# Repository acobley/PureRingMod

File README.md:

View this project on [CADLAB.io](https://cadlab.io/project/1337). 

# PureRingMod
A Eurorack ring modulator.

1:  Balanced input suitable for a SM58 
2: Carrier and Mod levels should accept 10Vpp.   Level controls on each.
3: Mixer on Mic in and Carrier
4: Mixer on the output of the ring mod chip and Carrier in.  This allows the uint to act as a mic input to eurorack
5: Gain control on the output stage, I found this useful to avoid clipping on the output
6: Dual output sockets.  It's a bugbear of mine that more modules don't have dual output to avoid having to use a splitter module to send the signal to more than one output.

Design Andy C
From a design by Roman Sowa
CC BY 3.0

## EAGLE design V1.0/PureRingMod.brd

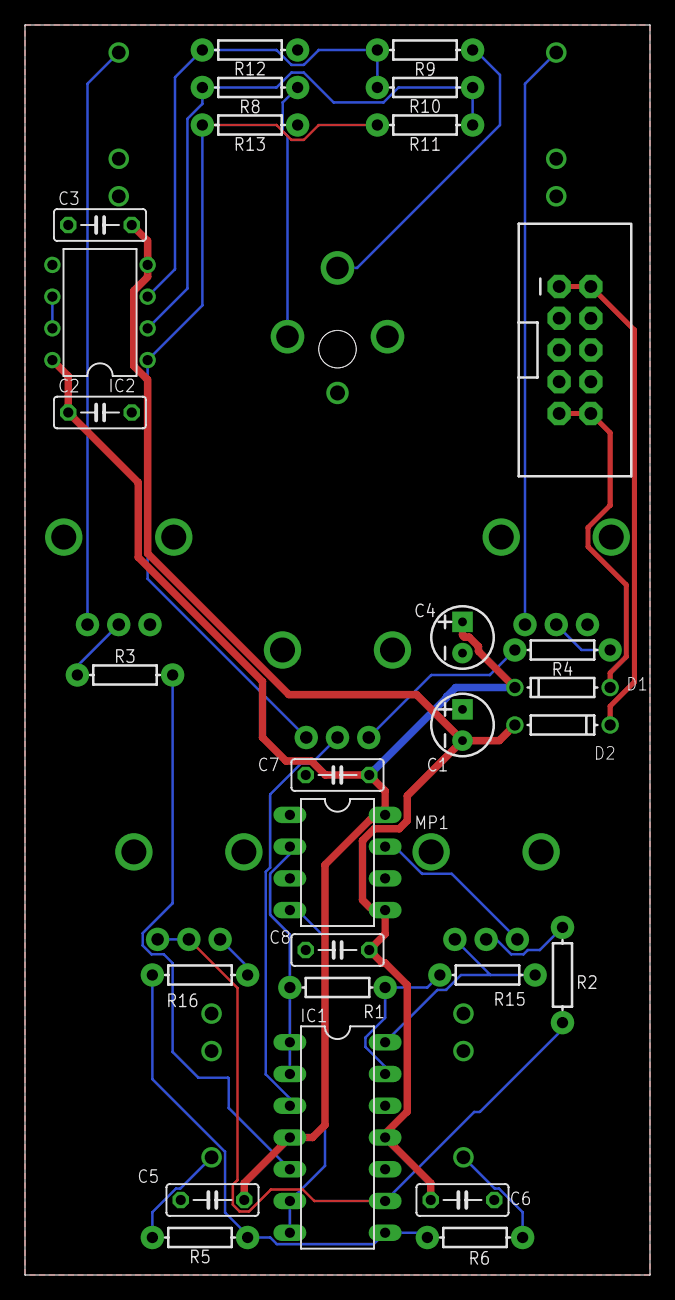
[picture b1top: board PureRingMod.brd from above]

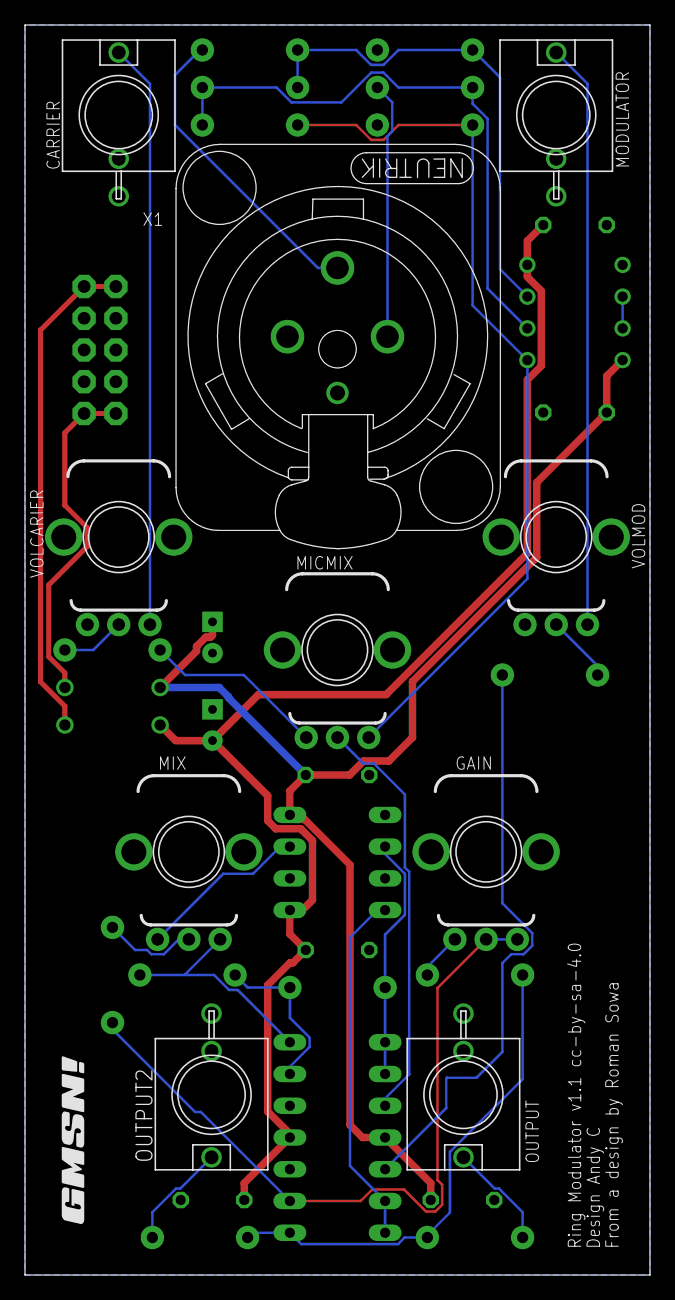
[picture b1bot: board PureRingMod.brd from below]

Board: 2 copper layers, 50.0 x 100.0 mm, 39 parts (11 on the bottom side), 29 nets.

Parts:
C1, C4: 10uF; CPOL-RADIAL-2.5MM-5MM
C2, C3, C5, C6, C7, C8: C050-025X075
CARRIER: JACK
D1: 1n4148; DO-1N4148
D2: 1N4148; DO-1N4148
GAIN: 9MMPOT; POT
IC1: TL074P; DIL14
IC2: TL072P; DIL08
MICMIX: 9MMPOT; POT
MIX: 9MMPOT; POT
MODULATOR: JACK
MP1: AD633-2_AD633AN; AD633-2_DIL08
OUTPUT: JACK
OUTPUT2: Output2; JACK
POWER: M05X2SHD; 2X5-SHROUDED
R1, R2, R3, R4, R5, R6, R8, R9, R10, R11, R12, R13, R15, R16: 330; AXIAL-0.3
U$2: GMSN!_LOGO
VOLCARIER: 9MMPOT; POT
VOLMOD: 9MMPOT; POT
X1: CON-NEUTRIK_AG_NC3FD-V

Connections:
+12V: C2.1, C4.1, C5.1, C7.1, D1.C, IC1.4, IC2.8, MP1.8
-12V: C1.2, C3.2, C6.2, C8.2, D2.A, IC1.11, IC2.4, MP1.5
GND: C1.1, C2.2, C3.1, C4.2, C5.2, C6.1, C7.2, C8.1, CARRIER.GND, CARRIER.NORM, IC1.10, IC1.12, IC2.5, MODULATOR.GND, MODULATOR.NORM, MP1.1, MP1.3, MP1.6, OUTPUT.GND, OUTPUT2.GND, POWER.3, POWER.4, POWER.5, POWER.6, POWER.7, POWER.8, R12.P$2, R13.P$1, VOLCARIER.P$1, VOLMOD.P$1, X1.1, X1.G
unnamed: IC1.1, IC1.2, MP1.2, R1.P$1
unnamed: IC1.6, IC1.7, MP1.4
unnamed: MIX.P$1, MP1.7
unnamed: IC1.14, MIX.P$3, R15.P$2
unnamed: GAIN.P$1, R16.P$1
unnamed: MIX.P$2, R2.P$1
unnamed: GAIN.P$2, GAIN.P$3, IC1.9, R2.P$2
unnamed: MICMIX.P$1, R4.P$2
unnamed: D1.A, POWER.9, POWER.10
unnamed: D2.C, POWER.1, POWER.2
unnamed: IC1.5, R3.P$2
unnamed: IC1.8, R5.P$1, R6.P$1, R16.P$2
unnamed: IC2.6, IC2.7
unnamed: IC1.13, R1.P$2, R15.P$1
unnamed: OUTPUT.TIP, R5.P$2
unnamed: CARRIER.TIP, VOLCARIER.P$3
unnamed: MODULATOR.TIP, VOLMOD.P$3
unnamed: R4.P$1, VOLCARIER.P$2
unnamed: R3.P$1, VOLMOD.P$2
unnamed: OUTPUT2.TIP, R6.P$2
unnamed: R8.P$1, X1.2
unnamed: R9.P$1, X1.3
unnamed: IC2.2, R8.P$2, R10.P$2, R11.P$1
unnamed: IC2.3, R9.P$2, R10.P$1, R12.P$1
unnamed: IC2.1, MICMIX.P$3, R11.P$2, R13.P$2
unnamed: IC1.3, MICMIX.P$2

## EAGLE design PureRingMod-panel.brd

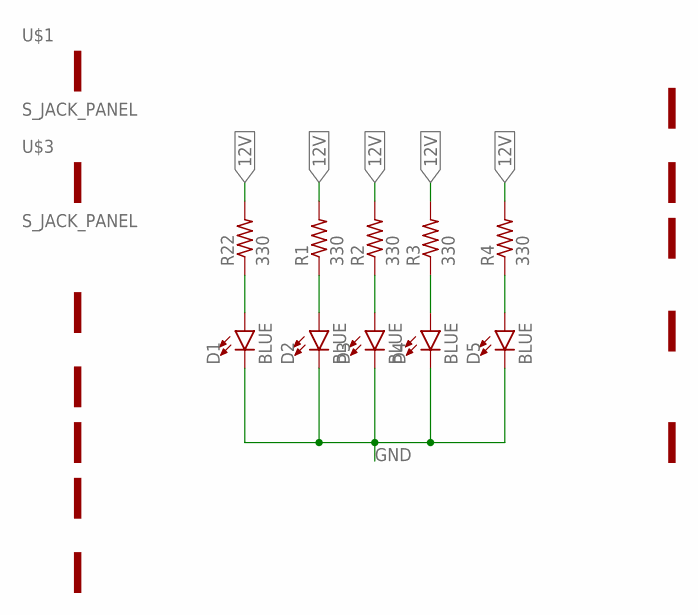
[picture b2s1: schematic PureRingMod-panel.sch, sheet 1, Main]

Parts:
D1, D2, D3, D4, D5: BLUE; LED-1206
R1, R2, R3, R4, R22: 330; R0805
U$1, U$3: S_JACK_PANEL
U$6, U$7, U$8, U$9, U$10: POT_PANEL
U$11: XLR_PANEL
U$12, U$13, U$14, U$15: MOUNTING_HOLE

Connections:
12V: R1.2, R2.2, R3.2, R4.2, R22.2; also elsewhere on the board
GND: D1.C, D2.C, D3.C, D4.C, D5.C; also elsewhere on the board
unnamed: D1.A, R22.1
unnamed: D2.A, R1.1
unnamed: D3.A, R2.1
unnamed: D4.A, R3.1
unnamed: D5.A, R4.1

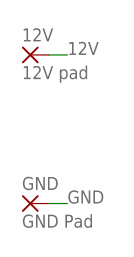
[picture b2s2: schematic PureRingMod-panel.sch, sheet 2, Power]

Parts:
12V: 12V pad; 1,6/0,8
GND: GND Pad; 1,6/0,8

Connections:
12V: 12V.1; also elsewhere on the board
GND: GND.1; also elsewhere on the board

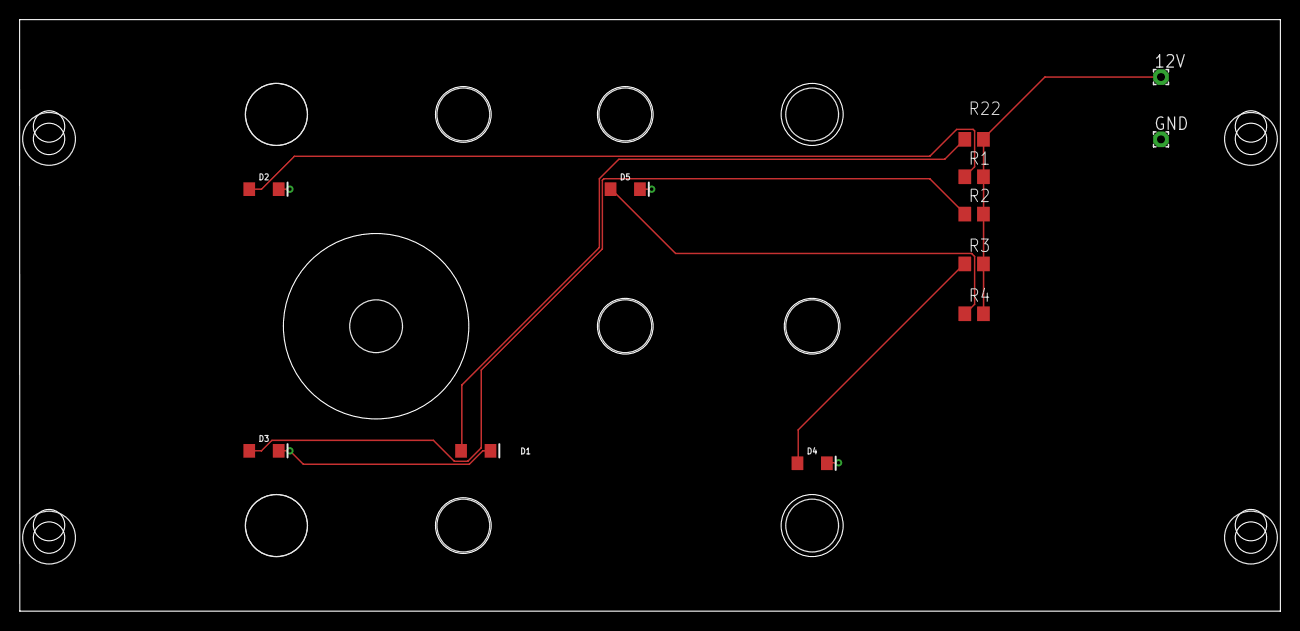
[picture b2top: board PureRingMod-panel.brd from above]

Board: 2 copper layers, 128.5 x 60.3 mm, 27 parts (1 on the bottom side), 7 nets.

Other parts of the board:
U$2: GMSN!_LOGO
U$4, U$5: S_JACK_PANEL; S_JACK_PANEL@1

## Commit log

2018-10-03 Init design
2018-10-03 Backlink to CADLAB.io has been added.
2018-10-03 Power to TL072
2018-10-04 removed backup files
2018-10-13 added mix control
2018-10-13 Added input circuit emualtion for use in https://www.falstad.com/circuit/
2018-10-13 updated components in feedback circuit of preamp
2018-10-13 Corrected values on input circuit
2018-10-13 corrected input components
2018-10-14 added missing parts
2018-10-14 Changed output circuit values
2018-10-14 modified input mic circuit
2018-10-14 Fixed input
2018-10-14 Fixed output socket
2018-10-17 minor change
2018-10-19 fixed -12V to Tl074
2018-10-19 removed ac/Dc switched input
2018-10-19 ripped up board
2018-10-21 latest
2018-10-21 Fixed wiring errors
2018-10-27 updated board
2018-10-31 V1.0 board
2018-11-01 added panel design (PCB)
2018-11-01 Panel Design
2018-11-03 design of panel
2018-11-05 added BOM
2018-11-05 updated BOM
2018-11-07 upadeted panel
2018-11-07 latest panel board using 'components'
2018-11-19 frozen V1.0 directory
2018-11-29 Panel layout and routing
2018-11-29 Added Version 1 archive

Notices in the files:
V1.0/PureRingMod.brd:
Ring Modulator v1.1 cc-by-sa-4.0
parts and their libraries:
SparkFun-LED: Licensing: Creative Commons ShareAlike 4.0 International - https://creativecommons.org/licenses/by-sa/4.0
